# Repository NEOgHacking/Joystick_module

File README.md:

# Joystick_module
This is a simple module designed for the purpose of having a simple joystick to be able to interact with the hackxpansion console. It uses a simple 5 button clicky style arcade joystick so navigation in the menu will be a breeze!!!

The design has 3 parts:
## Schematic

## PCB

## Case

Onshape link for the case:

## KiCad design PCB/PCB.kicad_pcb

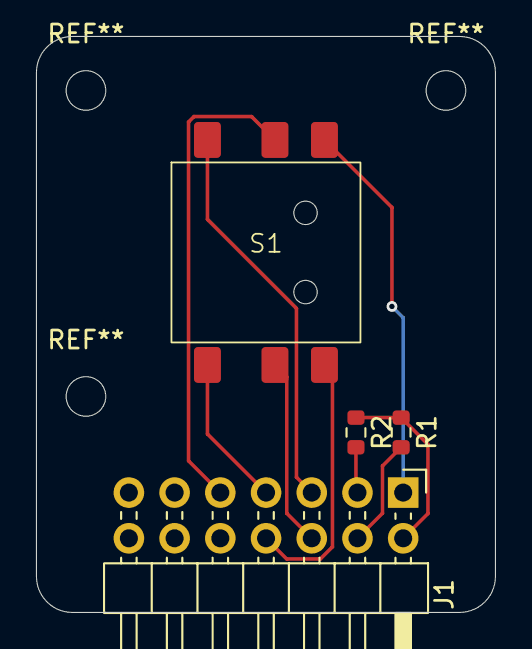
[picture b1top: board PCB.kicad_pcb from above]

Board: 2 copper layers, 25.5 x 32.0 mm, 4 parts (0 on the bottom side), 9 nets.

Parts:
J1: PinHeader_2x07_P2.54mm_Horizontal
R1, R2: R; R_0603_1608Metric
S1: Joystick; Untitled

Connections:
+3V3: J1.2 (3V3), R1.1, R2.1
GND: J1.1 (GND), S1.4 (Public)
unnamed: J1.7 (GPI02), S1.1 (F3)
unnamed: J1.5 (GPIO0), S1.6 (F1)
unnamed: J1.6 (GPIO1), S1.2 (F2)
unnamed: J1.8 (GPIO3), S1.3 (F4)
unnamed: J1.9 (GPIO4), S1.5 (F5)
unnamed: J1.3 (MD0), R2.2
unnamed: J1.4 (MD1), R1.2
